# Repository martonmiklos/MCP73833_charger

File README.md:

# MCP73833_charger
Small micro USB - 1S liion/lipo charger

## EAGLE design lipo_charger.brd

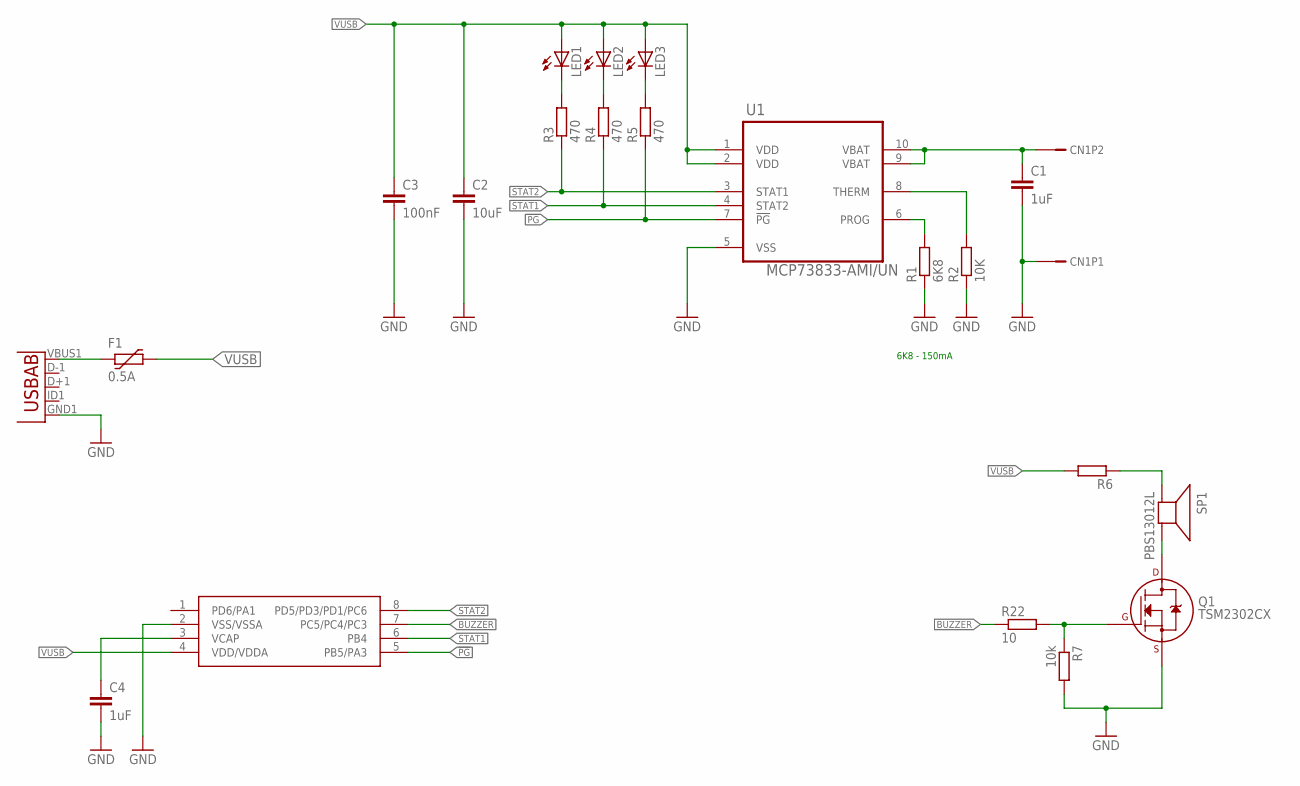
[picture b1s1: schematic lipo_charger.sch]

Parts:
C1: 1uF; C0805
C2: 10uF; C0805
C3: 100nF; C0603
C4: 1uF; C0603
CN1: B2B-PH-K-S
F1: 0.5A; PTC0805
LED1, LED2, LED3: LED0603; CHIPLED_0603
Q1: TSM2302CX; SOT-23
R1: 6K8; R0603
R2: 10K; R0603
R3, R4, R5: 470; R0603
R6: R-EU_R0603; R0603
R7: 10k; R0603
R22: 10; R0603
SP1: PBS13012L; AL60P
U1: MCP73833-AMI/UN; SOP50P490X110-10N
U2: STM8S001J3; SO8N
X1: USB-ABIN&OUT; USB-AB-MICRO-SMD-V03-IN&OUT

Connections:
!PG: R5.1, U1.7 (!PG), U2.5 (PB5/PA3)
BUZZER: R22.1, U2.7 (PC5/PC4/PC3)
BUZZER_BEFORERES: Q1.1 (G), R7.1, R22.2
GND: C1.2, C2.2, C3.2, C4.2, CN1.1, Q1.2 (S), R1.1, R2.1, R7.2, U1.5 (VSS), U2.2 (VSS/VSSA), X1.GND1 (GND)
MCP73833_PROG: R1.2, U1.6 (PROG)
MCP73833_THERM: R2.2, U1.8 (THERM)
unnamed: R6.1, SP1.1 (+)
unnamed: LED1.C, R3.2
unnamed: LED2.C, R4.2
unnamed: LED3.C, R5.2
unnamed: Q1.3 (D), SP1.2 (-)
STAT1: R4.1, U1.4 (STAT2), U2.6 (PB4)
STAT2: R3.1, U1.3 (STAT1), U2.8 (PD5/PD3/PD1/PC6)
VBAT: C1.1, CN1.2, U1.9 (VBAT), U1.10 (VBAT)
VCAP: C4.1, U2.3 (VCAP)
VUSB: C2.1, C3.1, F1.2, LED1.A, LED2.A, LED3.A, R6.2, U1.1 (VDD), U1.2 (VDD), U2.4 (VDD/VDDA)
VUSB_UNFUSED: F1.1, X1.VBUS1 (VBUS)

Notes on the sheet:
6K8 - 150mA

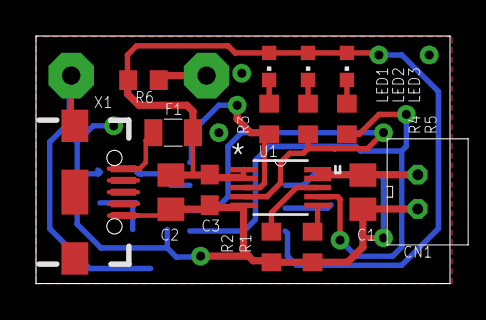
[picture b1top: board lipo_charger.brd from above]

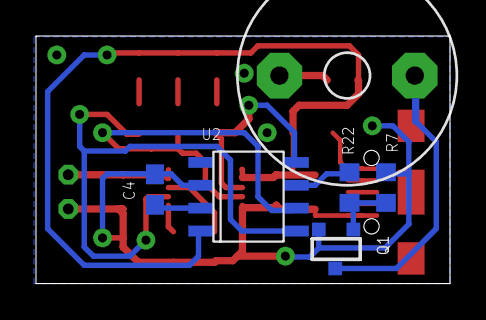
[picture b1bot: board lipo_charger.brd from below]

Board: 2 copper layers, 23.0 x 13.8 mm, 22 parts (6 on the bottom side), 17 nets.

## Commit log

2018-12-14 Added files

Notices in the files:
parts and their libraries:
SparkFun: Licensing: CC v3.0 Share-Alike You are welcome to use this library for commercial purposes.
